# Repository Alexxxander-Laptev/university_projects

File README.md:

# university_projects
This repository will store all my university projects

В этом репозитории находится большая часть отчетов, файлов с исходным кодом, справочных материалов и файлов с лекциями, накопленных за весь период обучения на бакалавриате и в магистратуре.

Иерархическая структура репозитория представляет из себя набор директорий для каждого курса обучения по отдельности, каждая из которых содержит директории с названиями соответствующих предметов на кириллице или латинице в зависимости от содержания.

Кроме этих директорий, в отдельной директории с одноименным названием представлены файлы со справочными материалами, в директории "Projects" представлен проект на C для одной из лабораторных работ, связанной со знакомством с библиотекой libusb.

В директории "Установщики" представлены архивы или торенты с различными программами, которые требовались в процессе обучения (но не вообще со всеми необходимыми), в директории "Arduino" представлен тестовый проект для работы с термопарой и проект генератора персонажей Dangeous and Dragons, который являлся моим проектом для выпускной квалификационной работы на бакалавриате и ряде НИР на 3 - 4 курсах.

Директория "InfoBase" содержит базы данных для лабораторных работ по 1С в курсе ИСТ (в том числе мое финальное задание). Кроме того, в репозитории находится файл "settings.json", который можно использовать для сборки pdf-файлов с использованием xelatex (шаблоны кафедры для отчетов по лабораторным работам, НИР и ВКР используют xelatex) на локальной машине с использованием VSCode.

Все отчеты, которые оформлены с использованием tex можно считать шаблонами, поскольку, если это ВКР, то они прошли нормоконтроль, а если это НИР, то по итогу такие отчеты были приняты к защите. Отдельно можно обратить внимание на оформление магистрской дисертации (презентация и пояснительная записка), в шаблоне для презентаций внесены ряд изменений для обчеспечения его корректной работы с xelatex.

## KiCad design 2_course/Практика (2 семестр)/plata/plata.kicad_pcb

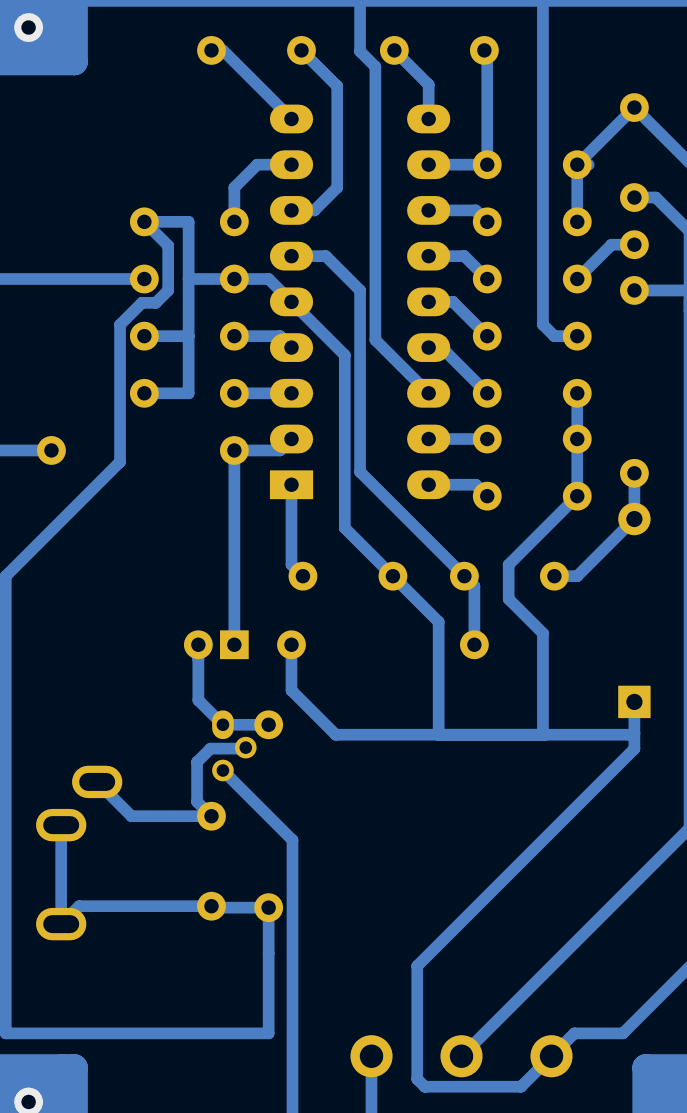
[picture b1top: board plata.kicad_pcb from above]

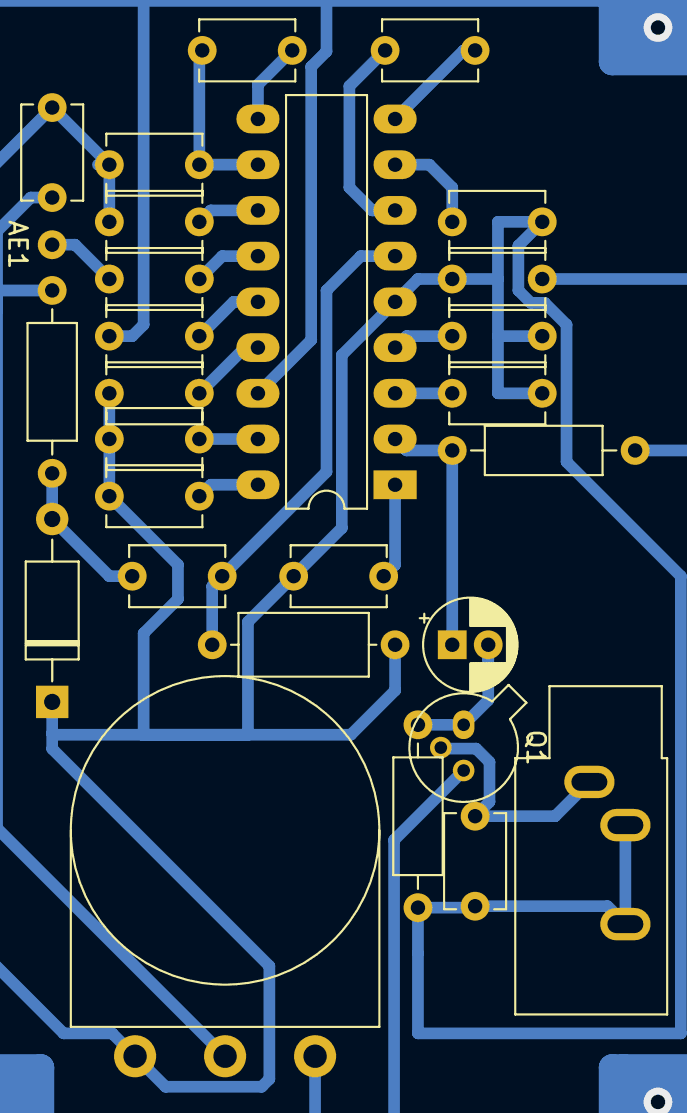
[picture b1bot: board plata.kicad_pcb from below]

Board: 2 copper layers, 28 parts (28 on the bottom side), 23 nets.

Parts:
AE1: Antenna; Banana_Jack_1Pin
C1, C10, C11, C12: 220п; C_Disc_D5.1mm_W3.2mm_P5.00mm
C2, C7: 150н; C_Disc_D5.1mm_W3.2mm_P5.00mm
C3: 33н; C_Disc_D5.1mm_W3.2mm_P5.00mm
C4, C17: 330п; C_Disc_D5.1mm_W3.2mm_P5.00mm
C5: 4700н; CP_Radial_D5.0mm_P2.00mm
C6: 15н; C_Disc_D5.1mm_W3.2mm_P5.00mm
C8, C9, C16: 10н; C_Disc_D5.1mm_W3.2mm_P5.00mm
C13: 150п; C_Disc_D5.1mm_W3.2mm_P5.00mm
C14, C18: 3.3н; C_Disc_D5.1mm_W3.2mm_P5.00mm
C15: 180п; C_Disc_D5.1mm_W3.2mm_P5.00mm
D1: KB121A; D_A-405_P10.16mm_Horizontal
J1: AudioJack3; Jack_3.5mm_CUI_SJ1-3533NG_Horizontal
L1: L; L_Axial_L7.0mm_D3.3mm_P10.16mm_Horizontal_Fastron_MICC
Q1: KT315; TO-18-3
R1: 47к; R_Axial_DIN0207_L6.3mm_D2.5mm_P10.16mm_Horizontal
R2: 22к; R_Axial_DIN0207_L6.3mm_D2.5mm_P10.16mm_Horizontal
R3: 100к; R_Axial_DIN0207_L6.3mm_D2.5mm_P10.16mm_Horizontal
RV1: СП-3; Potentiometer_Omeg_PC16BU_Vertical
U1: KC1066XA1; DIP-18_W7.62mm_LongPads

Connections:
+5V: C1.1, C2.2, C3.2, C4.1, C6.2, C7.1, C8.2, C9.1, C13.1, C14.1, C15.2, C16.1, D1.1, J1.R, J1.T, L1.1, R1.2, RV1.3, U1.5
GND: C9.2, C10.1, Q1.3, R2.2, RV1.1, U1.16
unnamed: AE1.1, C11.1
unnamed: C1.2, U1.18
unnamed: C2.1, U1.1
unnamed: C3.1, J1.S, Q1.2
unnamed: C4.2, U1.17
unnamed: C5.1, R2.1, U1.2
unnamed: C5.2, Q1.1, R1.1
unnamed: C6.1, U1.3
unnamed: C7.2, U1.15
unnamed: C8.1, U1.4
unnamed: C10.2, U1.14
unnamed: C11.2, U1.13
unnamed: C12.1, D1.2, R3.1
unnamed: C12.2, L1.2, U1.6
unnamed: C13.2, U1.12
unnamed: C14.2, C17.2, U1.11
unnamed: C15.1, U1.8
unnamed: C16.2, R3.2, RV1.2
unnamed: C17.1, U1.10
unnamed: C18.1, U1.9
unnamed: C18.2, U1.7

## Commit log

2024-02-29 Create 1_course
2024-02-29 Create Практика (1 семестр)
2024-03-02 Удаление файлов синхронизации с google drive
2024-03-02 Еще немного чистки
2024-03-06 Изменения в 5 лабе
2024-03-09 Первый этап наведения порядка
2024-03-09 еще больше изменений
2024-03-09 Последние крупные изменения
2024-03-09 Перенос баз данных
2024-03-14 Перерасчет последнего пункта
2024-03-24 Расчет лабы по нейросетям
2024-03-24 Создание отчета по 1 лабе
2024-03-24 Добавил документы латеха и некоторые другие
2024-04-14 Изменения в отчете по ПАК
2024-04-14 Начало второй лабораторной работы
2024-04-20 Отчет по роботу
2024-04-21 Сделана 2 лабораторная работа
2024-04-22 Дополнение отчета
2024-04-22 Убрал дублирование
2024-05-30 Изменение отчета по ПАК
2024-06-01 Конечный вариант лабораторной работы
2024-06-01 Отчет по лабе
2024-06-02 Код по превой лабораторной работе по робототехнике
2024-06-10 Отчет по лабе 1
2024-06-10 Исправлены ошибки со скоростью
2024-06-29 Добавлены лабы по веб и черновик НИРа
2024-06-30 Сформированы датасеты с животными
2024-07-06 Реализовано все для обучения нейронок по практике
2024-07-06 Сохранение результатов обучения для отчета
2024-07-06 Добавлен вывод ошибок первого и второго рода
2024-07-07 Тренировка на 100 эпох для отчета
2024-07-07 Добавлена визуализация матрицы ошибок
2024-07-07 Отчет по практике
2024-07-08 Доработан отчет
2024-09-20 Добавлен файл прошивки по робототехнике
2024-09-21 Добавлены документы для всех тем и сделана первая тема
2024-09-22 Добавлены презентации и доклады по первым двум темам
2024-09-29 Добавлен доклад по теме паттерны проектирования
2024-09-29 Добавлен доклад по теме Проблемы VR
2024-10-08 Сделаны отчеты по нескольким темам
2024-10-08 Добавлена pdf версия отчета
2024-10-13 Сделаны оставшиеся презентации и первая лаба по ИКС
2024-10-16 Исправленная таблица
2024-11-09 Сделаны заготовки для реализации обхода популярных видов капчи
2024-11-14 Разработка решателя капчи перенесена в отдельный репозиторий для удобства
2024-11-19 Измненено содержание отчета по 2 НИРу
2024-11-19 Дополнен отчет по НИРу
2024-11-22 Нарисованы блок-схемы алгоритмов и дописан отчет по НИР
2024-11-28 Изменил имя руководителя и добавил ключевые слова
2024-11-30 Добавил справочные материалы за весь период обучения
2024-11-30 Добавил еще некоторые справочные материалы
2024-11-30 Изменены справочные материалы
2024-11-30 Добавлена тренировочная сессия для лаб по машинному обучению
2024-11-30 Еще некоторые лабы по разным предметам, которые остались на флешке (возможно дублирование, но мне лень)
2024-11-30 Видео для робототехники
2024-12-01 Добавляю установщики и iso, которые могут пригодиться по учебе
2024-12-01 Торренты для альтиума и библиотека graphviz
2024-12-01 Учебная версия 1С
2024-12-02 Добавил ПДФ для НИР, изменил названия и рассортировал папку usb
2024-12-02 Начал отчет по эксплуатационной практике
2024-12-03 Добавлен еще 1 день
2024-12-04 Добавлен отчет за день
2024-12-05 Очередной день
2024-12-09 Добавлена презентация и доклад по НИР
2024-12-11 Добавлено несколько дней в отчет
2024-12-12 Добавил еще 1 день в отчет
2024-12-18 Добавлены несколько дней в отчет
2024-12-19 Дополнен отчет по практике
2024-12-21 Изменение в названии отчета
2024-12-29 Внесены изменения в доклад и презентацию
2024-12-30 Добавлен pdf презентации
2025-01-17 Добавлено начало отчета по первой лабе по компьютерному зрению
2025-01-20 Добавлены справочные материалы по курсу ОТИК
2025-01-25 Начал делать лабы по компьютерному зрению
2025-01-26 Добавлен код по 2 лабораторной работе (компьютерное зрение)
2025-01-26 Добавлена 3 и 4 лабораторные работы по компьютерному зрению
2025-01-26 Сделана 5 лабораторная работа по компьютерному зрению
2025-01-27 Добавлена 6 лаба по CV
2025-01-30 Сделана 7, 9 и 10 лабы по компьютерному зрению
2025-02-01 Добавлена 8 лаба по компьютерному зрению
2025-02-01 Переработана структура директории
2025-02-02 Составлен отчет по 1 лабе компьютерное зрение
2025-02-02 Создан отчет ко 2 лабе и добавлены заглавия для остальных
2025-02-02 Добавлен отчет по 6 лабе
2025-02-04 Добавлены отчеты по 9 и 10 лабораторным работам
2025-02-06 Добавлены 4 и 7 отчеты по лабораторным работам
2025-02-10 Оформлена 3 лаба
2025-02-13 Добавлен отчет по 5 лабораторной работе
2025-02-13 Исправлен отчет по 5 работе
2025-02-13 Добавлен отчет к 8 лабораторной работе
2025-02-13 Выполнено финальное задание
2025-02-14 Перемещены некоторые ресурсы
2025-02-18 Добавлен отчет по 1 лабе облачные технологии
2025-02-21 внесены изменения в отчет
2025-02-25 Репозиторий для лабы по R и графики
2025-03-19 Добавлены главы отсканированной книги
2025-04-20 Добавлен отчет по НИР и для конференции
2025-04-27 Добавлены доклады и презентации к НИР и конференции
2025-04-28 Добавлена статья для конференции Иордана
2025-05-01 Дописана статья
2025-05-01 Изменено название секции
2025-05-01 Сделана презентация
2025-05-02 Добавлена нумерация слайдов
2025-05-08 Добавлен отчет по послежнему НИРу и начата работа над оформлением диплома
2025-05-10 Переконфигурирован файл настроек, оформлен код программ
2025-05-10 Сделано черновое оформление первых двух глав
2025-05-12 Перекомпановка содержимого глав (обозначен план)
2025-05-12 Включены главы в главный файл
2025-05-13 Внесены изменения в 1 главу
2025-05-15 Заменены файлы по НИР
2025-05-17 Обновлен НИР за последний семестр
2025-05-18 Завершено оформление 1 главы ВКР магистра, добавлен отчет по преддипломной практике
2025-05-21 Добавлены некотрые ссылки к 1 главе, намечен план 2 главы
2025-05-23 Дополнена вторая глава диплома
2025-05-24 Закончена первая секция второй главы
2025-05-25 Оформлена часть секции про модели для текстовых CAPTCHA
2025-05-26 Частично доплненыо описание моделей для детекции объектов
2025-05-27 Закончено оформление второй главы в черновом варианте
2025-05-29 Исправлены некоторые формулировки в первой главе
2025-05-29 Внесены изменения во второй главе
2025-05-29 Окончательное черновое оформление первых двух глав диплома
2025-05-30 Переработаны ключевые моменты всех глав (нужно отдельно переработать информацию про аудио капчи)
2025-05-31 Переработан весь написанный ранее материал
2025-05-31 Отформатированно оформление списков
2025-05-31 Добавлено введение и заключение, удалена 4 глава
2025-06-02 Исправлен титульный лист, написан реферат, переработаны названия глав и секций
2025-06-02 Исправлены некоторые подзаголовки для большего соответствия стилистике
2025-06-03 Частично обновлен список литературы
2025-06-04 Дополнен список источников
2025-06-04 Частично по госту оформлен список литературы
2025-06-05 Оформлены оставшиеся источники (поправить длину ссылок)
2025-06-05 Исправлены ссылки
2025-06-06 Приложение разделено на 3 части, исправлены ссылки на него в тексте работы,добавлены ссылки во введении
2025-06-06 Добавлено экспертное заключение для конференции
2025-06-06 Приложения выровнены по правой стороне
2025-06-07 Удалены лишние файлы и проект диплома перенесен в отдельную папку
2025-06-07 Частично оформлена презентация и создан щаблон доклада
2025-06-08 Создана презентация к докладу, исправлены опечатки в дипломе
2025-06-08 Частично оформлен доклад
2025-06-08 Доделан доклад, добавлен слайд в презентацию
2025-06-11 Исправлены опечатки и неточности в перезентации
2025-06-11 Удален ненужный комментарий
2025-06-11 Удалене ненужный комментарий
2025-06-11 Исправлены комментарии
2025-06-11 Исправлены опечатки и описки во введении
2025-06-11 Изменена формулировка цели
2025-06-11 Исправлены формулировки в заключении
2025-06-11 Исправлены опечатки и формулировки в 1 главе
2025-06-11 Добавлен раздаточный материал, пересобраны документы
2025-06-11 Исправлены опечатки, частично перерисованы блок-схемы
2025-06-12 Добавлены шаблоны отзыва руководителя и рецензии
2025-06-12 Добавлено видео с примерами работы готовых моделей
2025-06-12 Исправлен файл с раздаточным материалом
2025-06-12 Переработан текст доклада
2025-06-15 Дополнен доклад
2025-06-17 Исправлено количество рисунков
2025-06-17 Исправлено количество страниц
2025-06-18 Дополнен отзыв руководителя
2025-06-18 Исправлено форматирование для MS Word
2025-06-18 Еще исправлено форматирование
2025-06-24 Изменена дата на титульнике в презентации (отказался играть в шахматы)
